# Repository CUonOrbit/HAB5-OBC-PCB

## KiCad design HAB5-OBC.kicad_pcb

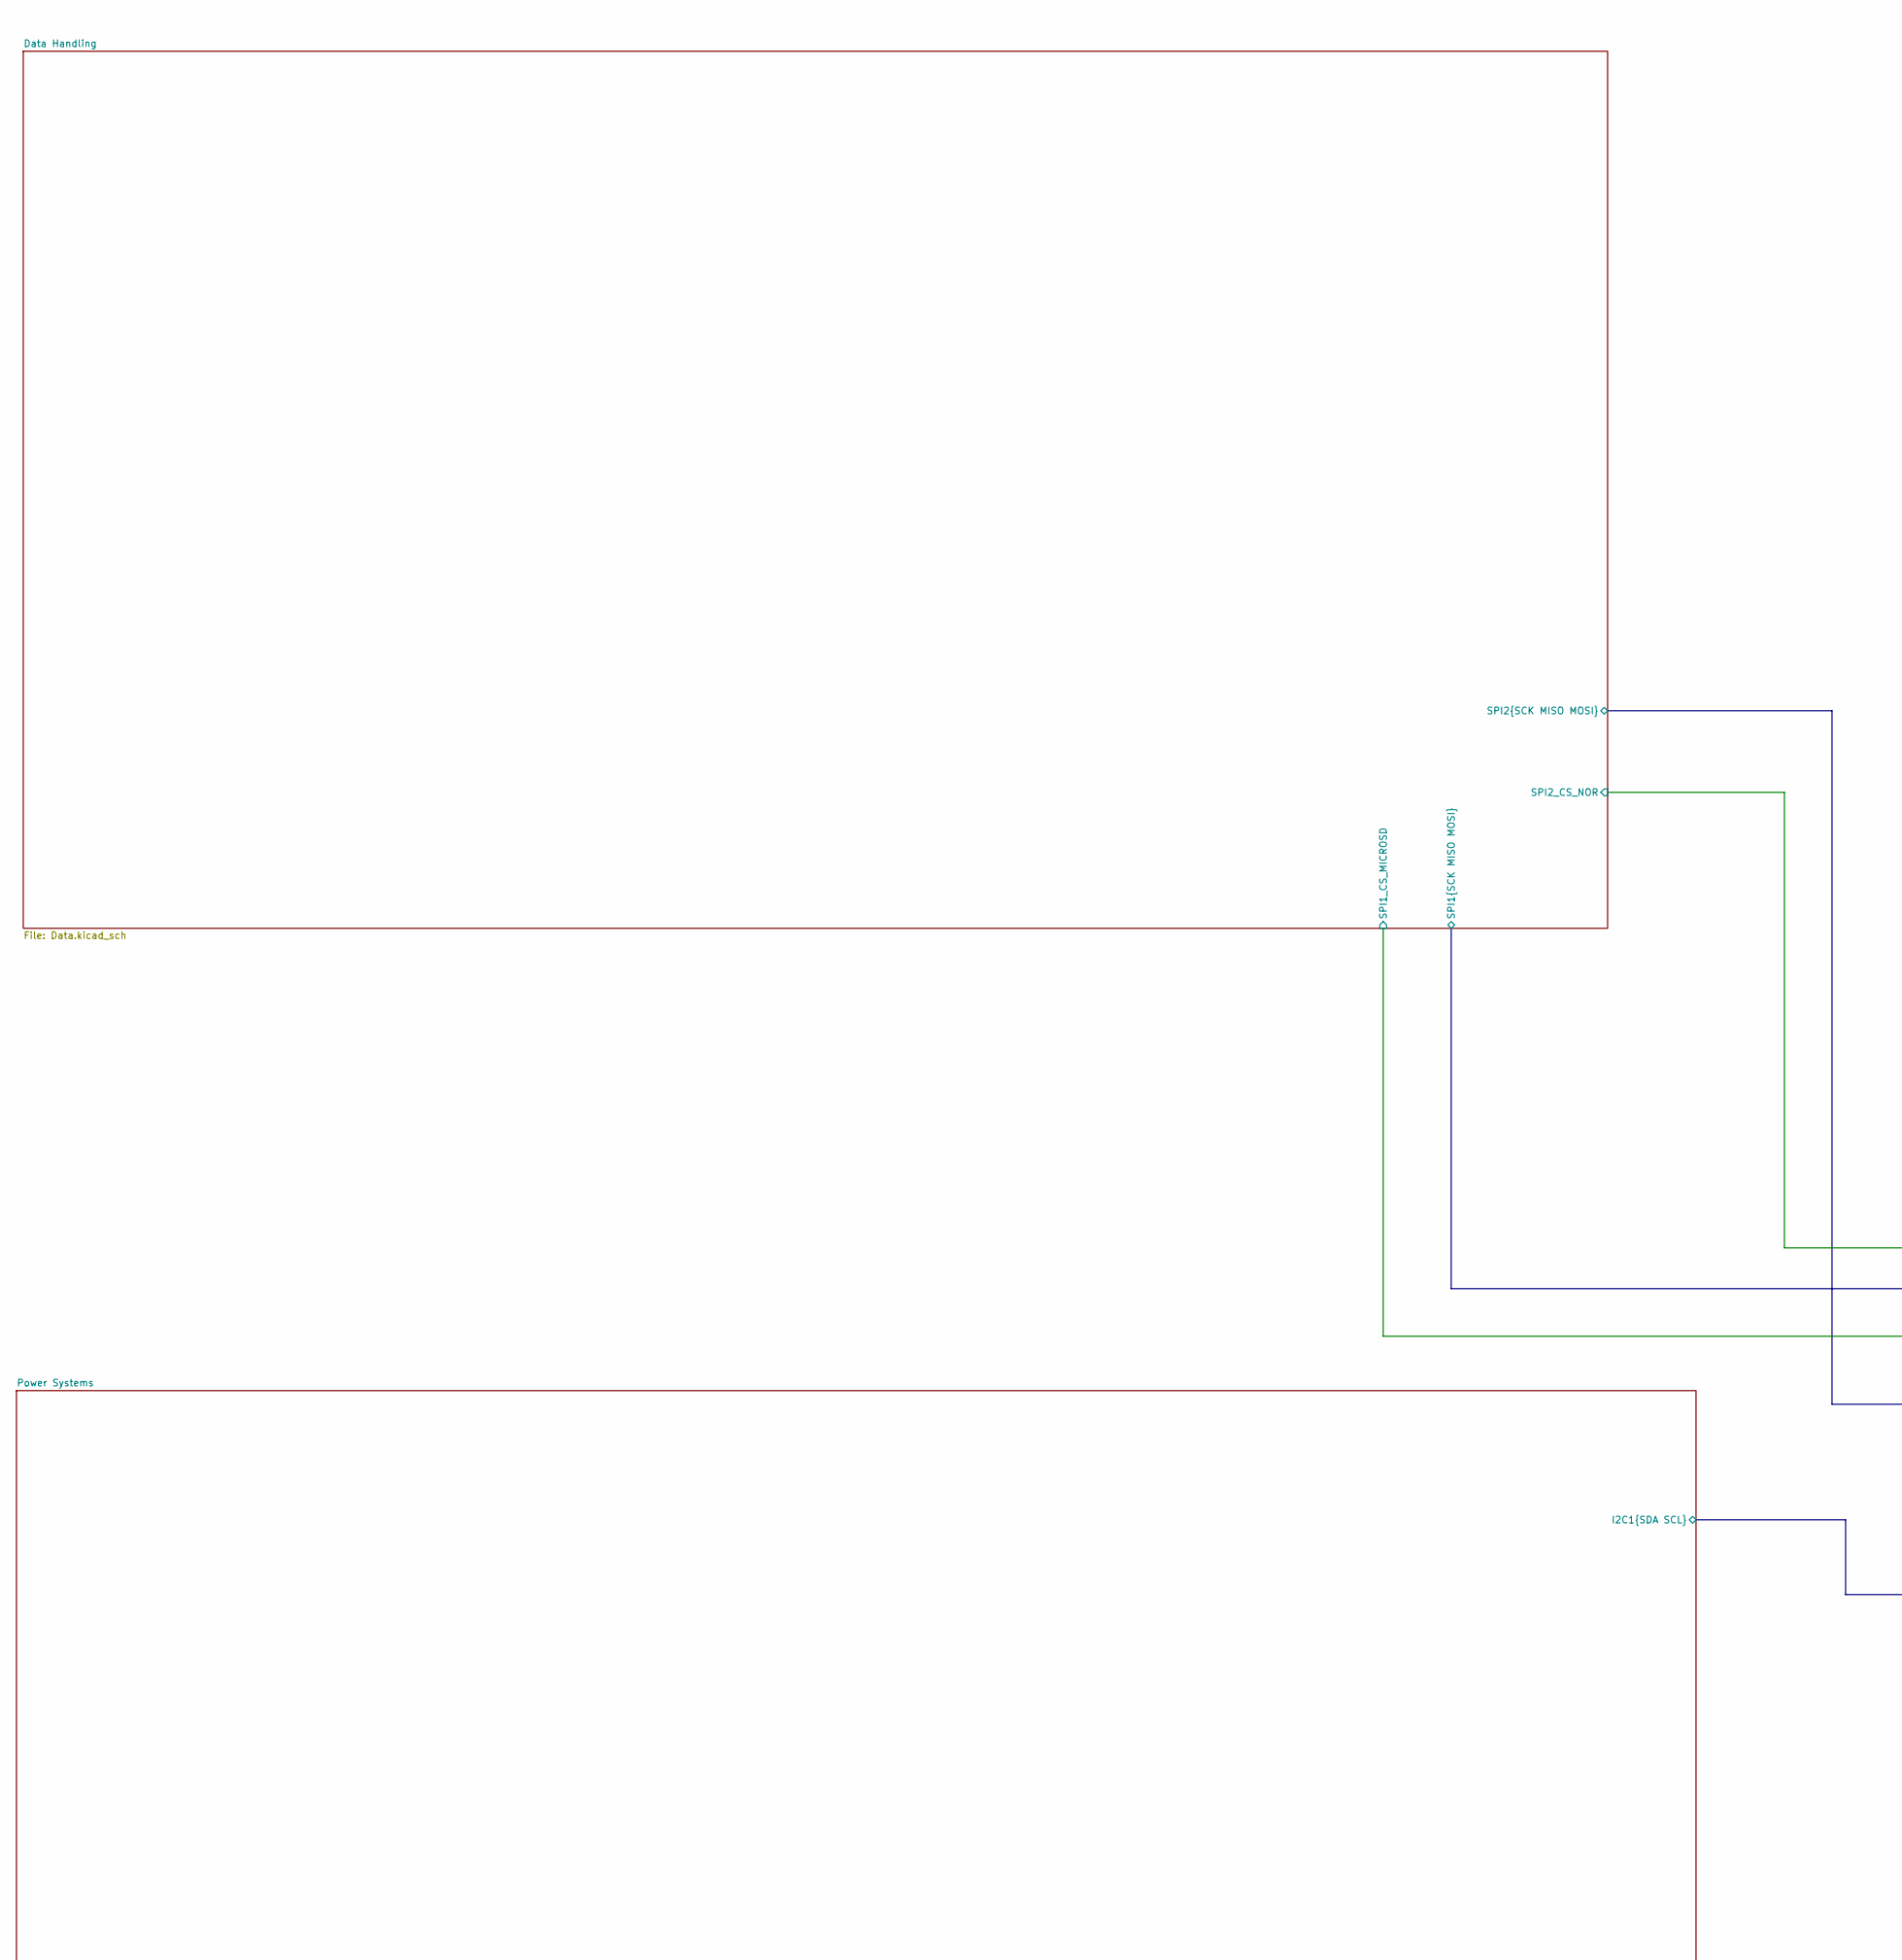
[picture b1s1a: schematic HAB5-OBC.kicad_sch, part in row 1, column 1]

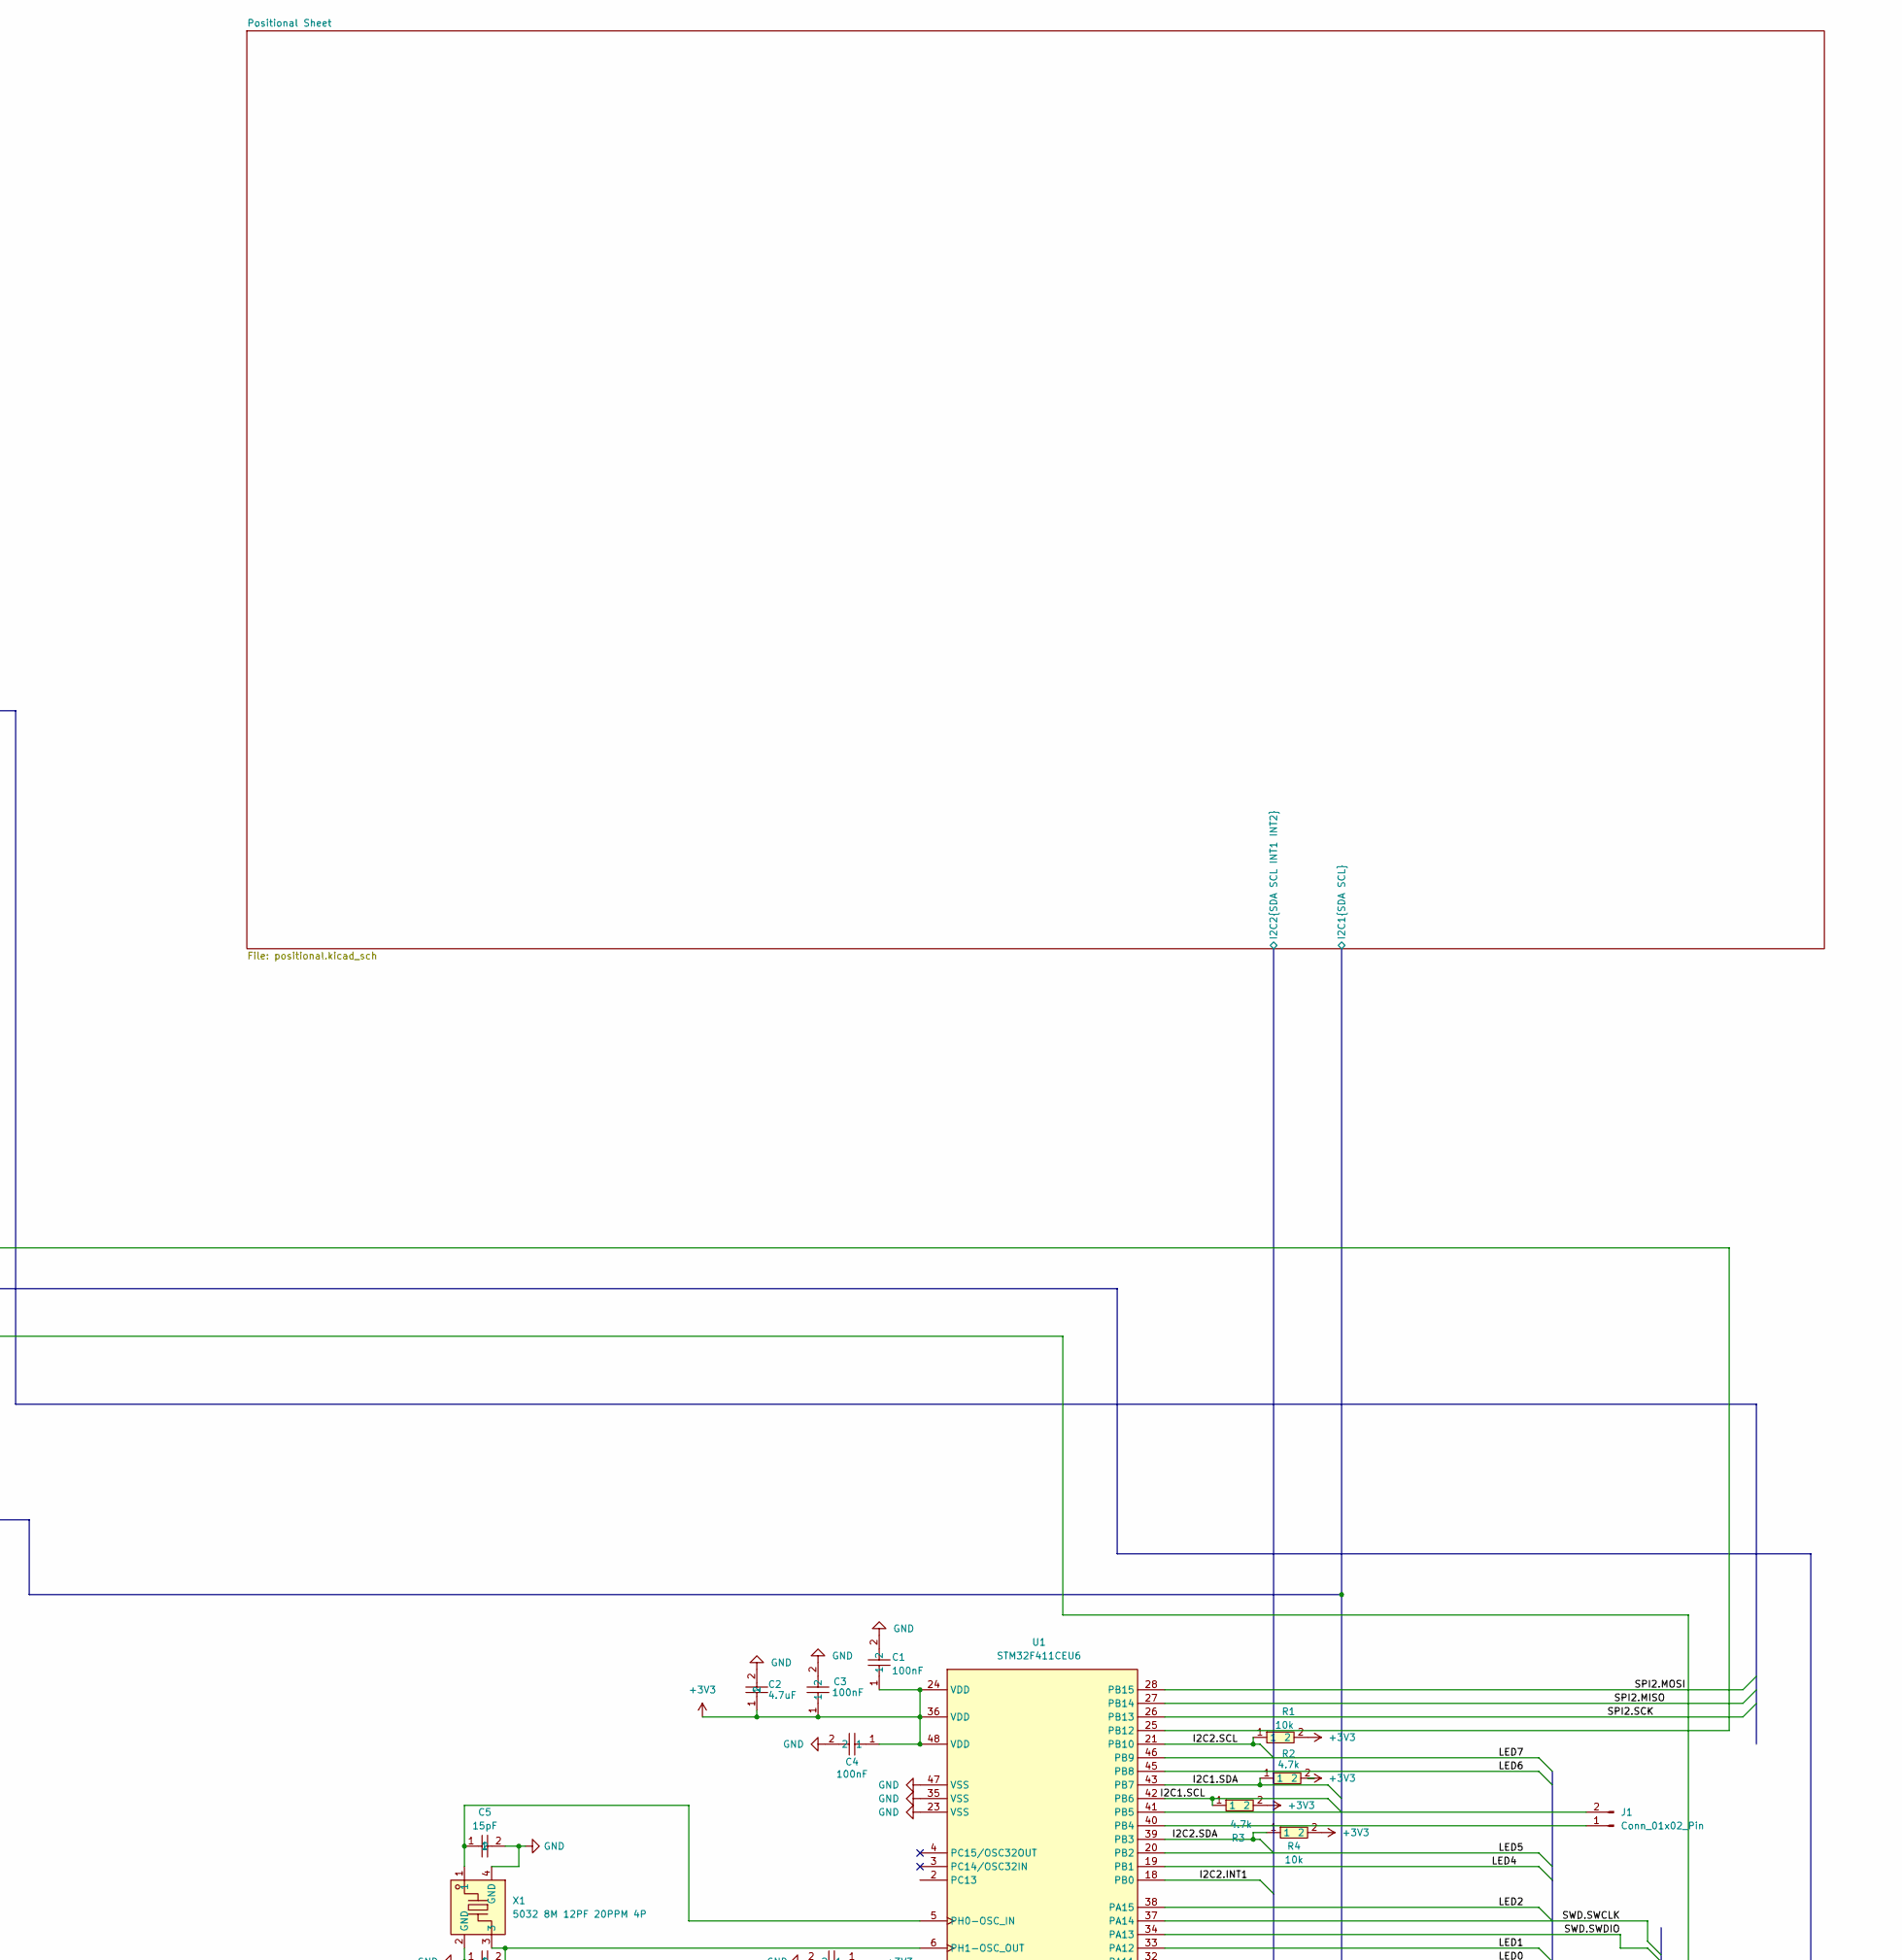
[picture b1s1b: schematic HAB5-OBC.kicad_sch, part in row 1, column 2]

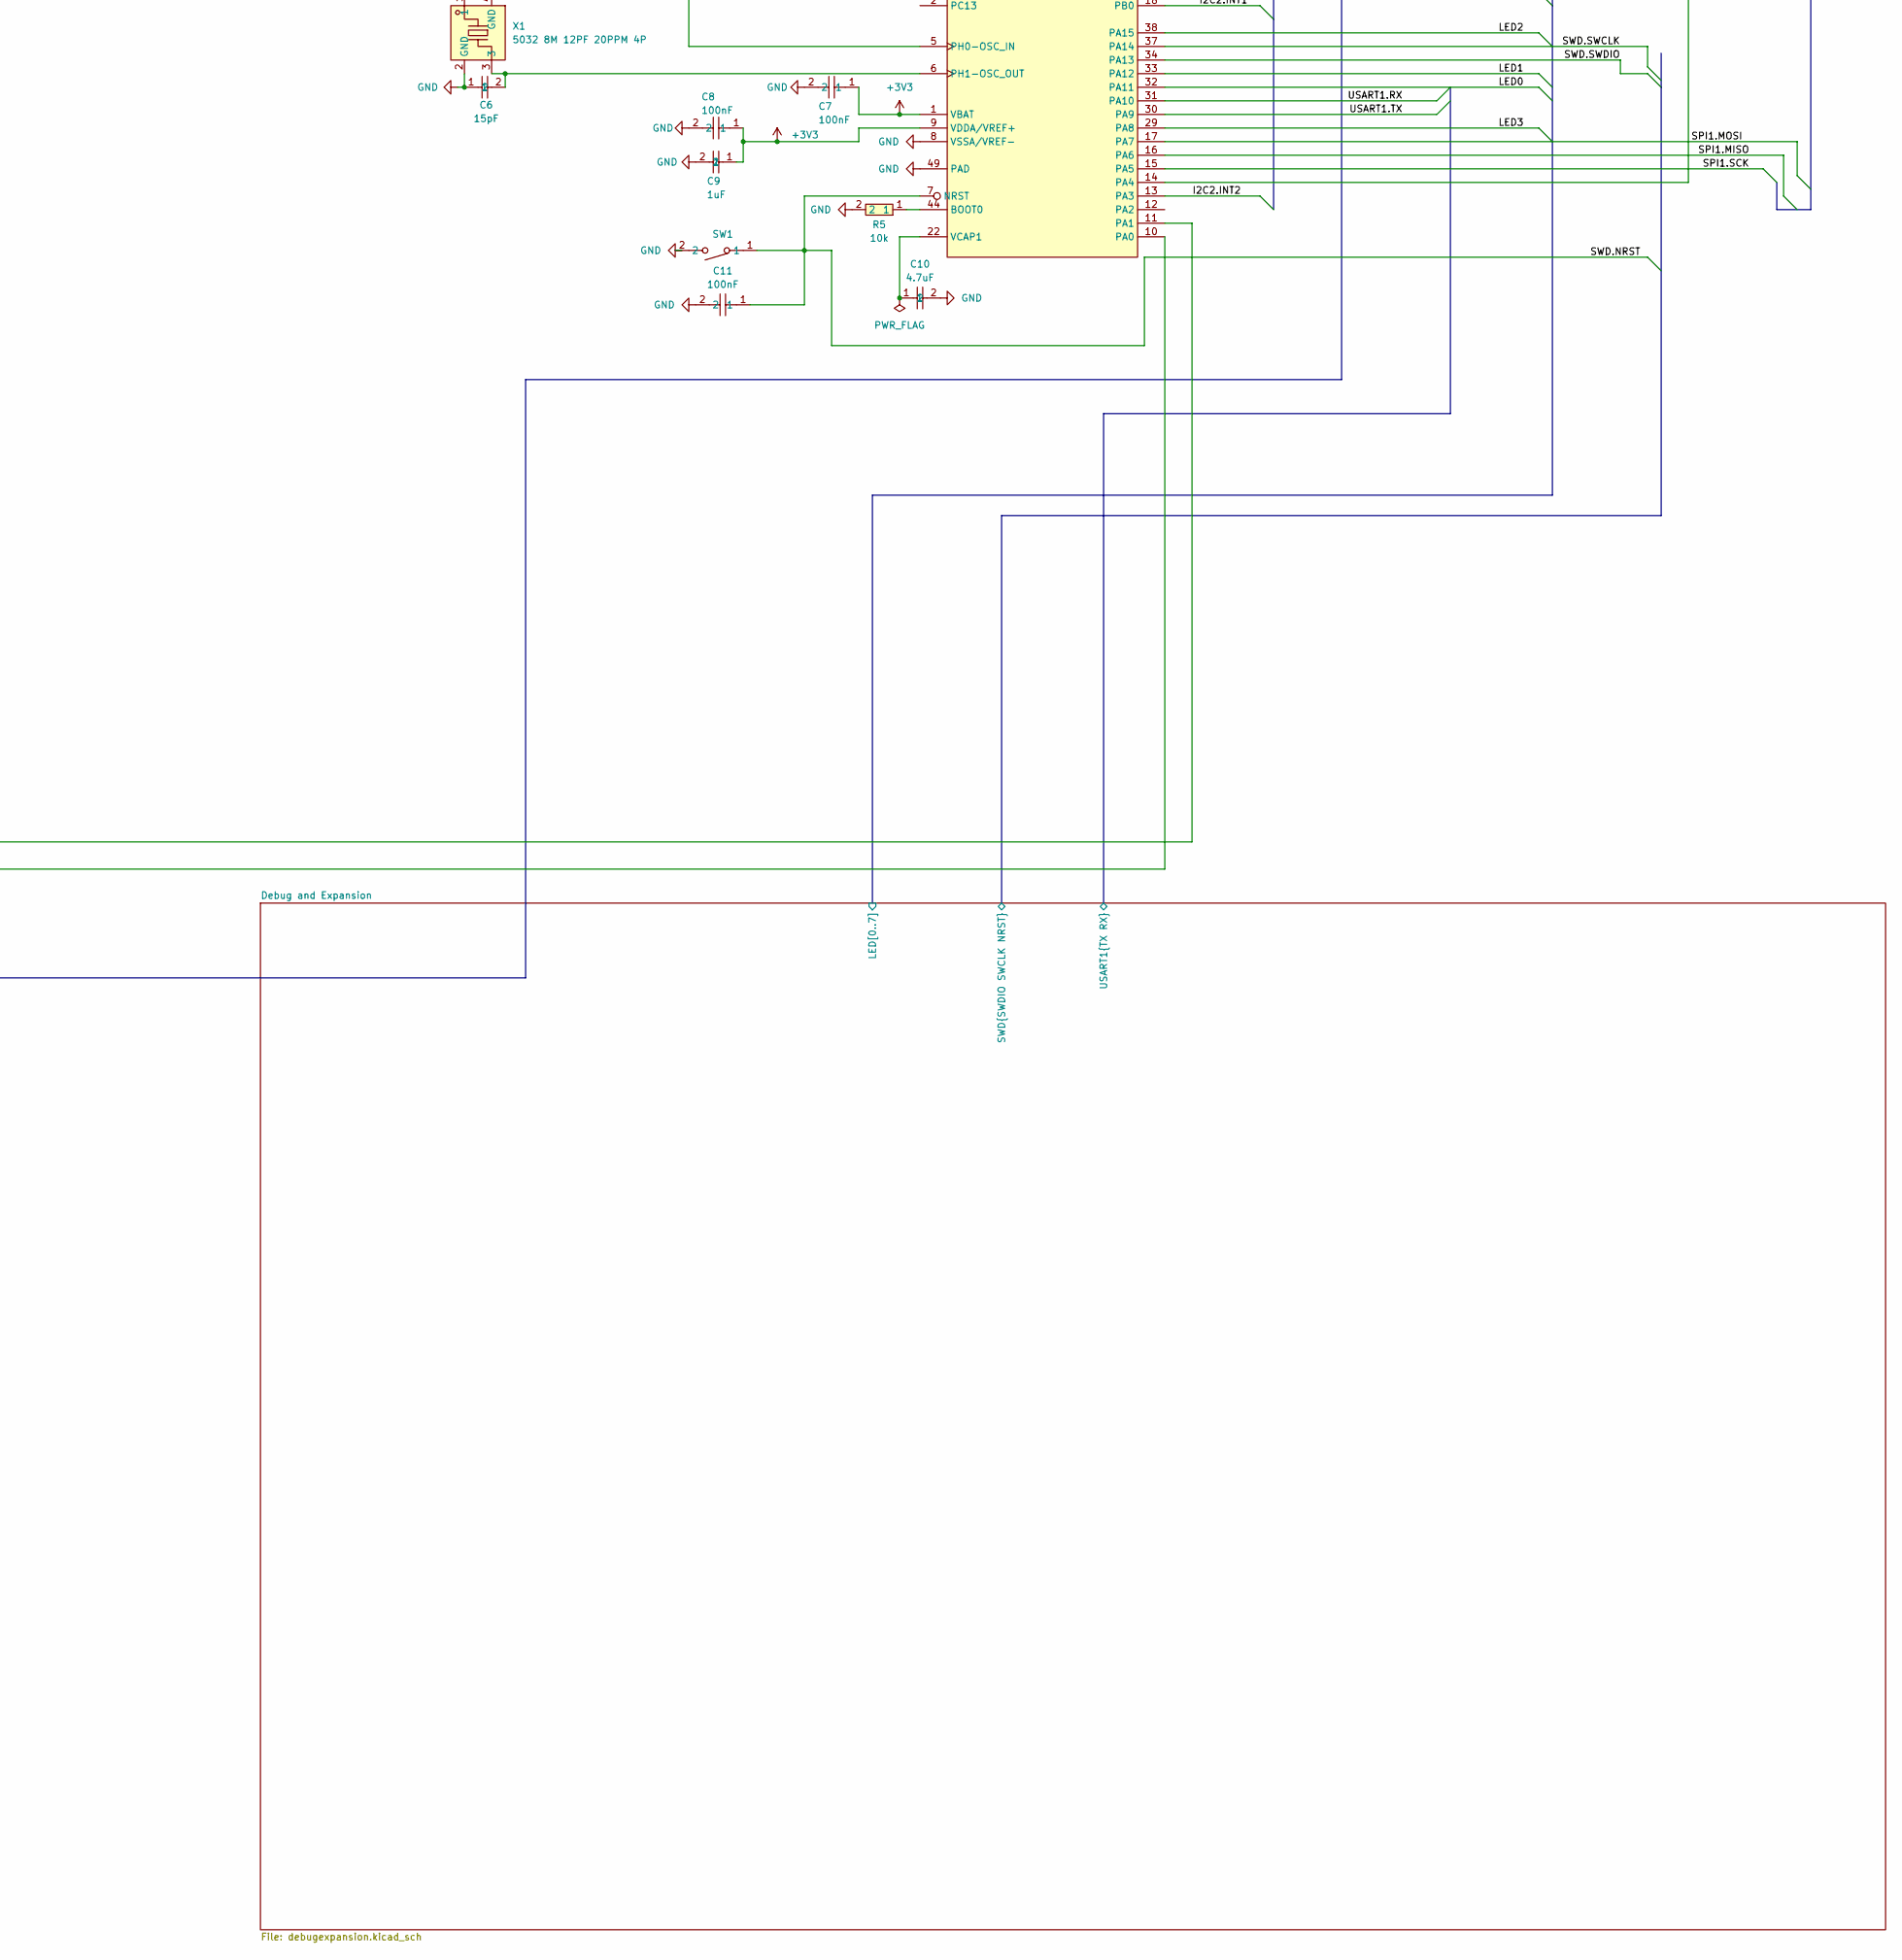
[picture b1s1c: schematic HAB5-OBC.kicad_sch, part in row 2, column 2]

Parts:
C1, C3, C4, C7, C8, C11: 100nF; C0402; MPN CL05B104KO5NNNC; LCSC Part C1525
C2, C10: 4.7uF; C1206; MPN 1206B475K500NT; LCSC Part C29823
C5, C6: 15pF; C0402; MPN 0402CG150J500NT; LCSC Part C1548
C9: 1uF; C0805; MPN CL21B105KBFNNNE; LCSC Part C28323
J1: Conn_01x02_Pin; PinHeader_1x02_P2.54mm_Vertical
R1, R4, R5: 10k; R0402; MPN 0402WGF1002TCE; LCSC Part C25744
R2, R3: 4.7k; R0603; MPN 0603WAF4701T5E; LCSC Part C23162
SW1: SW-SMD_L3.9-W3.0-P4.45; MPN TS-1088-AR02016; LCSC Part C720477
U1: STM32F411CEU6; UFQFPN-48_L7.0-W7.0-P0.50-BL-EP; MPN STM32F411CEU6; LCSC Part C60420
X1: 5032 8M 12PF 20PPM 4P; CRYSTAL-SMD_4P-L5.0-W3.2-BL_ECS; MPN 5032 8M 12PF 20PPM 4P; LCSC Part C5181482

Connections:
+3V3: C1.1, C2.1, C3.1, C4.1, C7.1, C8.1, C9.1, R1.2, R2.2, R3.2, R4.2, U1.1 (VBAT), U1.9 (VDDA/VREF+), U1.24 (VDD), U1.36 (VDD), U1.48 (VDD); also elsewhere on the board
/Data Handling/SPI1.CS: U1.14 (PA4); also elsewhere on the board
/Data Handling/SPI1.MISO: U1.16 (PA6); also elsewhere on the board
/Data Handling/SPI1.MOSI: U1.17 (PA7); also elsewhere on the board
/Data Handling/SPI1.SCK: U1.15 (PA5); also elsewhere on the board
/Data Handling/SPI2.MISO: U1.27 (PB14); also elsewhere on the board
/Data Handling/SPI2.MOSI: U1.28 (PB15); also elsewhere on the board
/Data Handling/SPI2.SCK: U1.26 (PB13); also elsewhere on the board
/Data Handling/SPI2_CS_NOR: U1.25 (PB12); also elsewhere on the board
/Debug and Expansion/LED0: U1.32 (PA11); also elsewhere on the board
/Debug and Expansion/LED1: U1.33 (PA12); also elsewhere on the board
/Debug and Expansion/LED2: U1.38 (PA15); also elsewhere on the board
/Debug and Expansion/LED3: U1.29 (PA8); also elsewhere on the board
/Debug and Expansion/LED4: U1.19 (PB1); also elsewhere on the board
/Debug and Expansion/LED5: U1.20 (PB2); also elsewhere on the board
/Debug and Expansion/LED6: U1.45 (PB8); also elsewhere on the board
/Debug and Expansion/LED7: U1.46 (PB9); also elsewhere on the board
/Debug and Expansion/SWD.NRST: C11.1, SW1.1, U1.7 (NRST); also elsewhere on the board
/Debug and Expansion/SWD.SWCLK: U1.37 (PA14); also elsewhere on the board
/Debug and Expansion/SWD.SWDIO: U1.34 (PA13); also elsewhere on the board
/Debug and Expansion/USART1.RX: U1.31 (PA10); also elsewhere on the board
/Debug and Expansion/USART1.TX: U1.30 (PA9); also elsewhere on the board
/Positional Sheet/I2C1.SCL: R3.1, U1.42 (PB6); also elsewhere on the board
/Positional Sheet/I2C1.SDA: R2.1, U1.43 (PB7); also elsewhere on the board
/Positional Sheet/I2C2.INT1: U1.18 (PB0); also elsewhere on the board
/Positional Sheet/I2C2.INT2: U1.13 (PA3); also elsewhere on the board
/Positional Sheet/I2C2.SCL: R1.1, U1.21 (PB10); also elsewhere on the board
/Positional Sheet/I2C2.SDA: R4.1, U1.39 (PB3); also elsewhere on the board
/Temperature/LMT84_OUT: U1.10 (PA0); also elsewhere on the board
/Temperature/NTC_MID: U1.11 (PA1); also elsewhere on the board
GND: C1.2, C2.2, C3.2, C4.2, C5.2, C6.1, C7.2, C8.2, C9.2, C10.2, C11.2, R5.2, SW1.2, U1.8 (VSSA/VREF-), U1.23 (VSS), U1.35 (VSS), U1.47 (VSS), U1.49 (PAD), X1.2 (GND), X1.4 (GND); also elsewhere on the board
unnamed: J1.1, U1.40 (PB4)
unnamed: J1.2, U1.41 (PB5)
unnamed: R5.1, U1.44 (BOOT0)
unnamed: C5.1, U1.5 (PH0-OSC_IN), X1.1
unnamed: C6.2, U1.6 (PH1-OSC_OUT), X1.3
unnamed: C10.1, U1.22 (VCAP1)

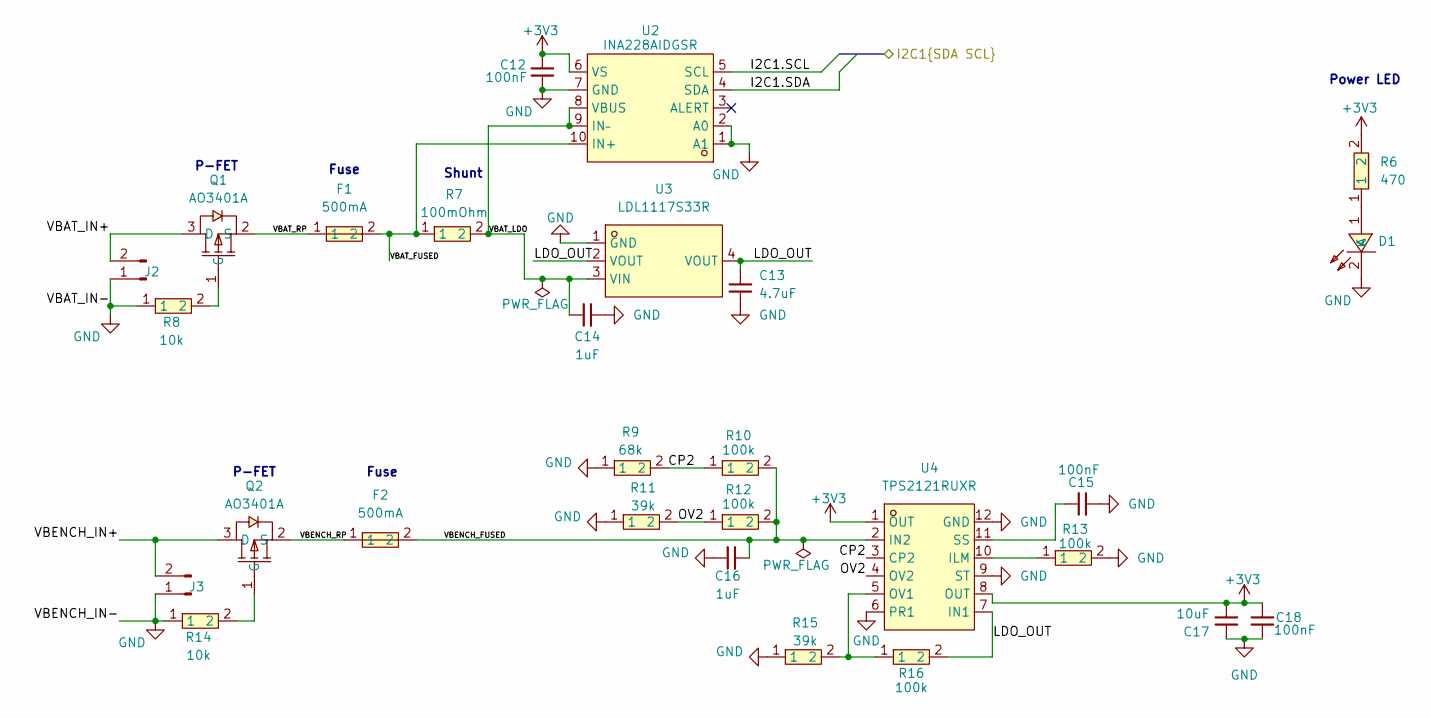
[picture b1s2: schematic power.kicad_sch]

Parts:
C12, C15, C18: 100nF; C0603; MPN CC0603KRX7R9BB104; LCSC Part C14663
C13: 4.7uF; C1206; MPN 1206B475K500NT; LCSC Part C29823
C14, C16: 1uF; C0805; MPN CL21B105KBFNNNE; LCSC Part C28323
C17: 10uF; C0805; MPN CL21A106KAYNNNE; LCSC Part C15850
D1: KT-0603R; LED-SMD_L1.6-W0.8-R-RD; MPN KT-0603R; LCSC Part C2286
F1, F2: 500mA; F1206; MPN 0466.500NRHF; LCSC Part C151133
J2: Molex_Micro-Fit_3.0_43650-0200_1x02_P3.00mm_Horizontal
J3: PinSocket_1x02_P2.54mm_Vertical
Q1, Q2: AO3401A; SOT-23_L2.9-W1.3-P1.90-LS2.4-BR; MPN AO3401A; LCSC Part C15127
R6: 470; R0603; MPN 0603WAF4700T5E; LCSC Part C23179
R7: 100mOhm; R2512; MPN LR2512-2AR100F4; LCSC Part C154690
R8, R14: 10k; R0603; MPN 0603WAF1002T5E; LCSC Part C25804
R9: 68k; R0603; MPN 0603WAF6802T5E; LCSC Part C23231
R10, R12, R13, R16: 100k; R0603; MPN 0603WAF1003T5E; LCSC Part C25803
R11, R15: 39k; R0603; MPN 0603WAF3902T5E; LCSC Part C23153
U2: INA228AIDGSR; VSSOP-10_L3.0-W3.0-P0.50-LS4.9-BL; MPN INA228AIDGSR; LCSC Part C2887910
U3: LDL1117S33R; SOT-223-4_L6.5-W3.5-P2.30-LS7.0-BR; MPN LDL1117S33R; LCSC Part C435835
U4: TPS2121RUXR; VQFN-HR-12_L2.5-W2.0-P0.50-BL; MPN TPS2121RUXR; LCSC Part C485916

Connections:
+3V3: C12.2, C17.1, C18.1, R6.2, U2.6 (VS), U4.1 (OUT), U4.8 (OUT); also elsewhere on the board
/Positional Sheet/I2C1.SCL: U2.5 (SCL); also elsewhere on the board
/Positional Sheet/I2C1.SDA: U2.4 (SDA); also elsewhere on the board
/Power Systems/CP2: R9.2, R10.1, U4.3 (CP2)
/Power Systems/LDO_OUT: C13.2, R16.2, U3.2 (VOUT), U3.4 (VOUT), U4.7 (IN1)
/Power Systems/OV2: R11.2, R12.1, U4.4 (OV2)
/Power Systems/VBAT_FUSED: F1.2, R7.1, U2.10 (IN+)
/Power Systems/VBAT_IN+: J2.2, Q1.3 (D)
/Power Systems/VBAT_LDO: C14.2, R7.2, U2.8 (VBUS), U2.9 (IN–), U3.3 (VIN)
/Power Systems/VBAT_RP: F1.1, Q1.2 (S)
/Power Systems/VBENCH_FUSED: C16.2, F2.2, R10.2, R12.2, U4.2 (IN2)
/Power Systems/VBENCH_IN+: J3.2, Q2.3 (D)
/Power Systems/VBENCH_RP: F2.1, Q2.2 (S)
GND: C12.1, C13.1, C14.1, C15.1, C16.1, C17.2, C18.2, D1.2 (K), J2.1, J3.1, R8.1, R9.1, R11.1, R13.2, R14.1, R15.1, U2.1 (A1), U2.2 (A0), U2.7 (GND), U3.1 (GND), U4.6 (PR1), U4.9 (ST), U4.12 (GND); also elsewhere on the board
unnamed: D1.1 (A), R6.1
unnamed: Q1.1 (G), R8.2
unnamed: Q2.1 (G), R14.2
unnamed: R13.1, U4.10 (ILM)
unnamed: R15.2, R16.1, U4.5 (OV1)
unnamed: C15.2, U4.11 (SS)

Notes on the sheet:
P-FET
Fuse
Power LED
Shunt

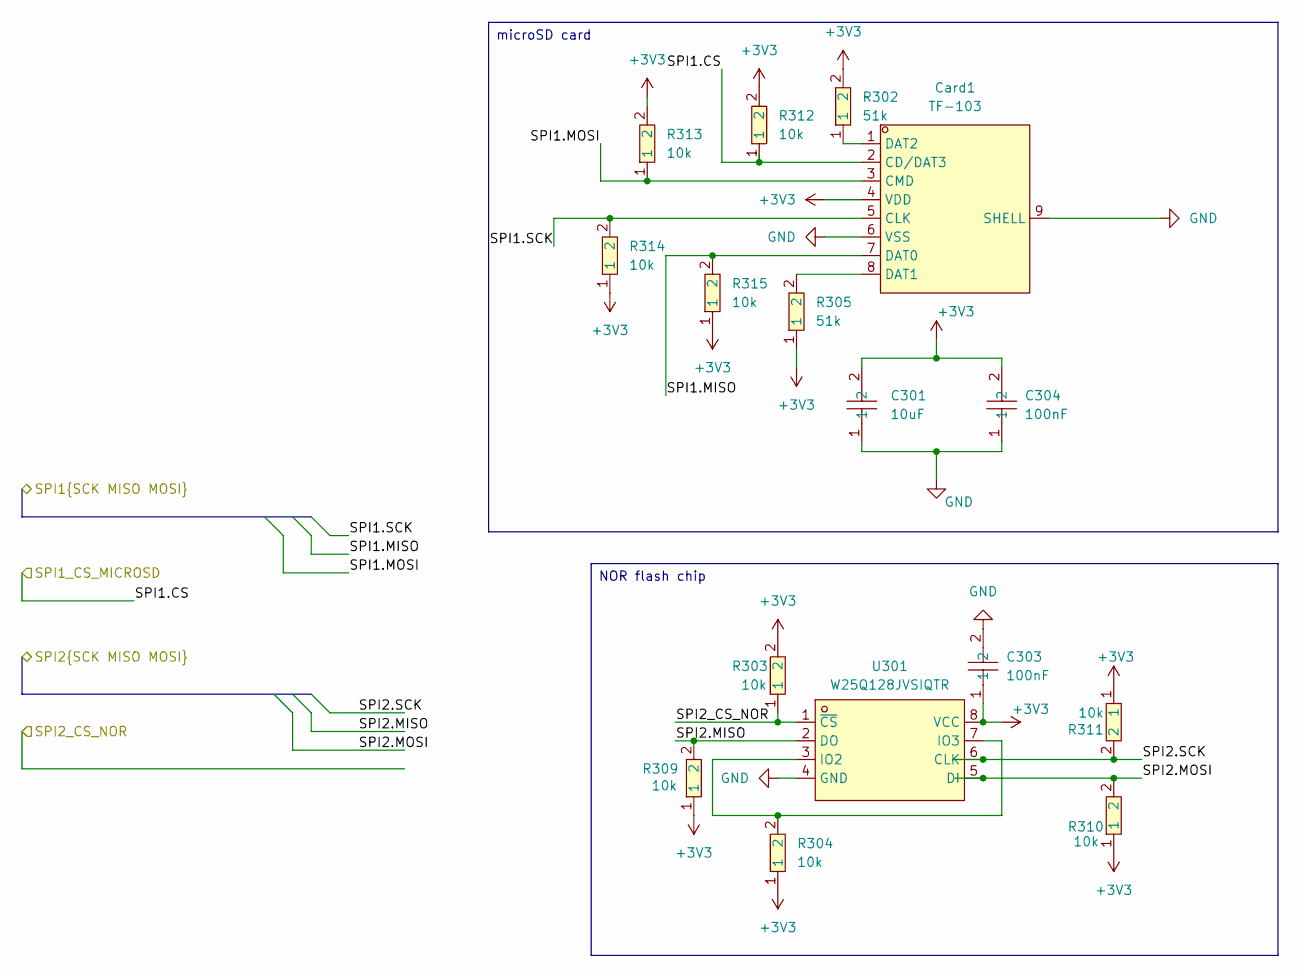
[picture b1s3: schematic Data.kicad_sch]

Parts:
C301: 10uF; C0805; MPN CL21A106KAYNNNE; LCSC Part C15850
C303, C304: 100nF; C0402; MPN CL05B104KO5NNNC; LCSC Part C1525
Card1: TF-103; TF-SMD_TF-103; MPN TF-103; LCSC Part C266611
R302, R305: 51k; R0603; MPN 0603WAF5102T5E; LCSC Part C23196
R303, R304, R309, R310, R311, R312, R313, R314, R315: 10k; R0402; MPN 0402WGF1002TCE; LCSC Part C25744
U301: W25Q128JVSIQTR; SOIC-8_L5.3-W5.3-P1.27-LS8.0-BL; MPN W25Q128JVSIQ; LCSC Part C97521

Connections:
+3V3: C301.2, C303.1, C304.2, Card1.4 (VDD), R302.2, R303.2, R304.1, R305.1, R309.1, R310.1, R311.1, R312.2, R313.2, R314.1, R315.1, U301.8 (VCC); also elsewhere on the board
/Data Handling/SPI1.CS: Card1.2 (CD/DAT3), R312.1; also elsewhere on the board
/Data Handling/SPI1.MISO: Card1.7 (DAT0), R315.2; also elsewhere on the board
/Data Handling/SPI1.MOSI: Card1.3 (CMD), R313.1; also elsewhere on the board
/Data Handling/SPI1.SCK: Card1.5 (CLK), R314.2; also elsewhere on the board
/Data Handling/SPI2.MISO: R309.2, U301.2 (DO); also elsewhere on the board
/Data Handling/SPI2.MOSI: R310.2, U301.5 (DI); also elsewhere on the board
/Data Handling/SPI2.SCK: R311.2, U301.6 (CLK); also elsewhere on the board
/Data Handling/SPI2_CS_NOR: R303.1, U301.1 (~CS); also elsewhere on the board
GND: C301.1, C303.2, C304.1, Card1.6 (VSS), Card1.9 (SHELL), U301.4 (GND); also elsewhere on the board
unnamed: Card1.8 (DAT1), R305.2
unnamed: Card1.1 (DAT2), R302.1
unnamed: R304.2, U301.3 (IO2), U301.7 (IO3)

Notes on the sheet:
NOR flash chip
microSD card

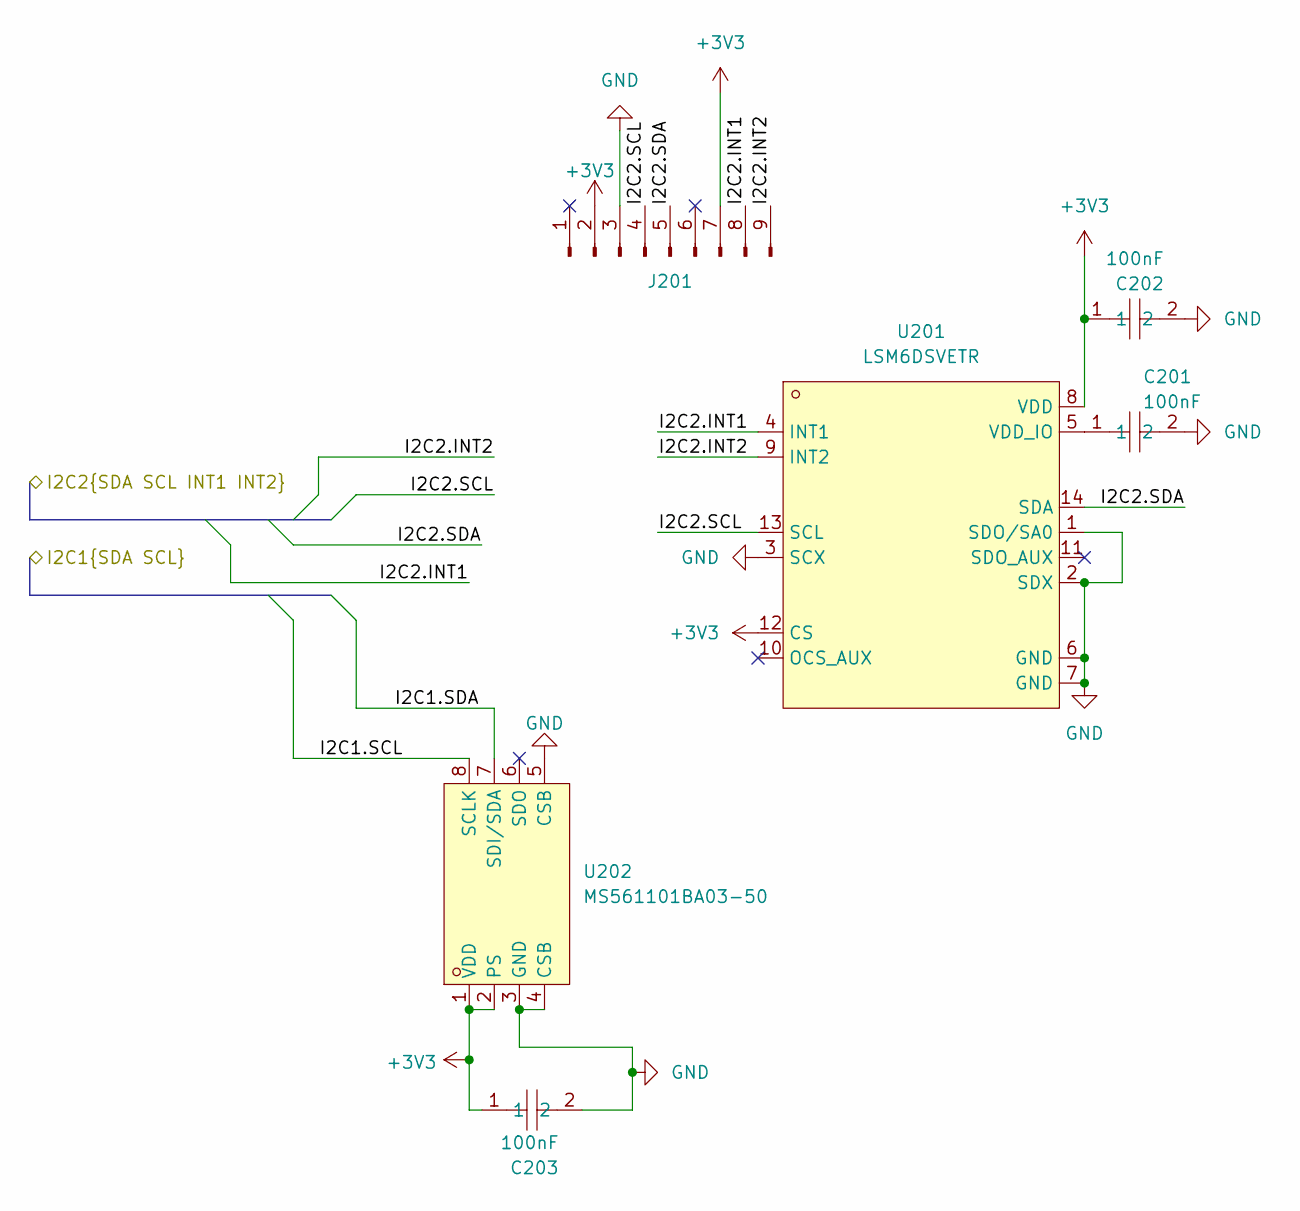
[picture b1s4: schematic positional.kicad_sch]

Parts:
C201, C202, C203: 100nF; C0402; MPN CL05B104KO5NNNC; LCSC Part C1525
J201: Conn_01x09_Pin; PinSocket_1x09_P2.54mm_Vertical
U201: LSM6DSVETR; LGA-14_L3.0-W2.5-P0.50-TL; MPN LSM6DSVETR; LCSC Part C41785564
U202: MS561101BA03-50; SENSORS-SMD_MS5611-01BA03; MPN MS561101BA03-50; LCSC Part C15639

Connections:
+3V3: C202.1, C203.1, J201.2, J201.7, U201.8 (VDD), U201.12 (CS), U202.1 (VDD), U202.2 (PS); also elsewhere on the board
/Positional Sheet/I2C1.SCL: U202.8 (SCLK); also elsewhere on the board
/Positional Sheet/I2C1.SDA: U202.7 (SDI/SDA); also elsewhere on the board
/Positional Sheet/I2C2.INT1: J201.8, U201.4 (INT1); also elsewhere on the board
/Positional Sheet/I2C2.INT2: J201.9, U201.9 (INT2); also elsewhere on the board
/Positional Sheet/I2C2.SCL: J201.4, U201.13 (SCL); also elsewhere on the board
/Positional Sheet/I2C2.SDA: J201.5, U201.14 (SDA); also elsewhere on the board
GND: C201.2, C202.2, C203.2, J201.3, U201.1 (SDO/SA0), U201.2 (SDX), U201.3 (SCX), U201.6 (GND), U201.7 (GND), U202.3 (GND), U202.4 (CSB), U202.5 (CSB); also elsewhere on the board
unnamed: C201.1, U201.5 (VDD_IO)

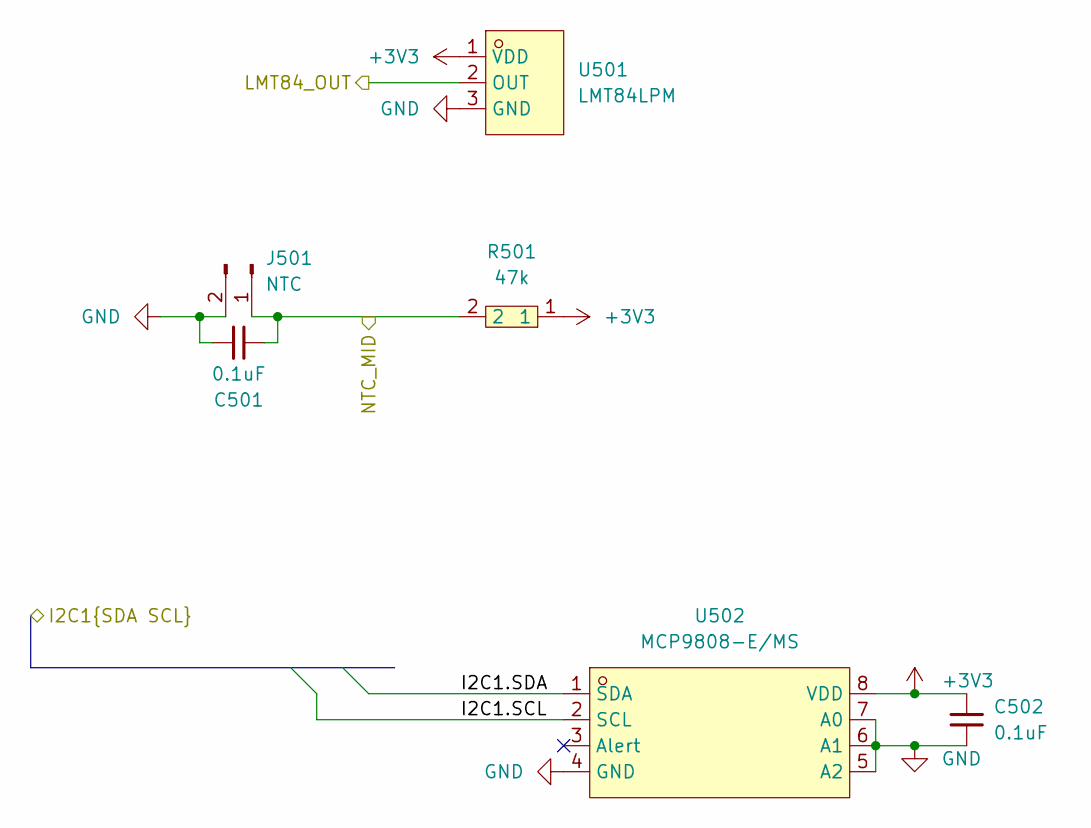
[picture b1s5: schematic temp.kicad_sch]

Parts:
C501, C502: 0.1uF; C0603; MPN CC0603KRX7R9BB104; LCSC Part C14663
J501: NTC; Molex_Micro-Fit_3.0_43650-0200_1x02_P3.00mm_Horizontal
R501: 47k; R0805; MPN 0805W8F4702T5E; LCSC Part C17713
U501: LMT84LPM; TO-92-3_L4.9-W3.7-P2.54-L; MPN LMT84LPM; LCSC Part C2877244
U502: MCP9808-E/MS; MSOP-8_L3.0-W3.0-P0.65-LS4.9-BL; MPN MCP9808-E/MS; LCSC Part C94847

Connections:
+3V3: C502.1, R501.1, U501.1 (VDD), U502.8 (VDD); also elsewhere on the board
/Positional Sheet/I2C1.SCL: U502.2 (SCL); also elsewhere on the board
/Positional Sheet/I2C1.SDA: U502.1 (SDA); also elsewhere on the board
/Temperature/LMT84_OUT: U501.2 (OUT); also elsewhere on the board
/Temperature/NTC_MID: C501.2, J501.1, R501.2; also elsewhere on the board
GND: C501.1, C502.2, J501.2, U501.3 (GND), U502.4 (GND), U502.5 (A2), U502.6 (A1), U502.7 (A0); also elsewhere on the board
